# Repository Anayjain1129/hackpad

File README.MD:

# Hack

### Why did I make it?
As I use hyprland user, I really needed a quick way to switch between windows without having using the keyboard shortcuts So ,I designed the Hackpad(hack)

### What was the hardest part about this ?
I had tons of issues with making the Firmware, as I'm on arch linux too I got too many errors. but at the last I figured out everything.

### Bill of Materials
 - 1x Seeed XIAO RP2040
 - 2x LED_SK6812MINI_PLCC4_3.5x3.5mm_P1.75mm
 - 6x SW_Cherry_MX_1.00u_PCB
 - 6x Blank DSA keycaps (Either White or Red)
 - Case (all black or a mix of Black and White)

### Schematic

---

### PCB 

---

### Case
- Bottom

- Top

-Built project

# Youtube Link
https://youtube.com/shorts/4EpmZ8gcD6c?si=dydtyU4dkYbHrrX3

# Reboot changes 
https://drive.google.com/file/d/1OqpE0TkTVKWNDCLAZDDclW11vvze6mBZ/view?usp=sharing

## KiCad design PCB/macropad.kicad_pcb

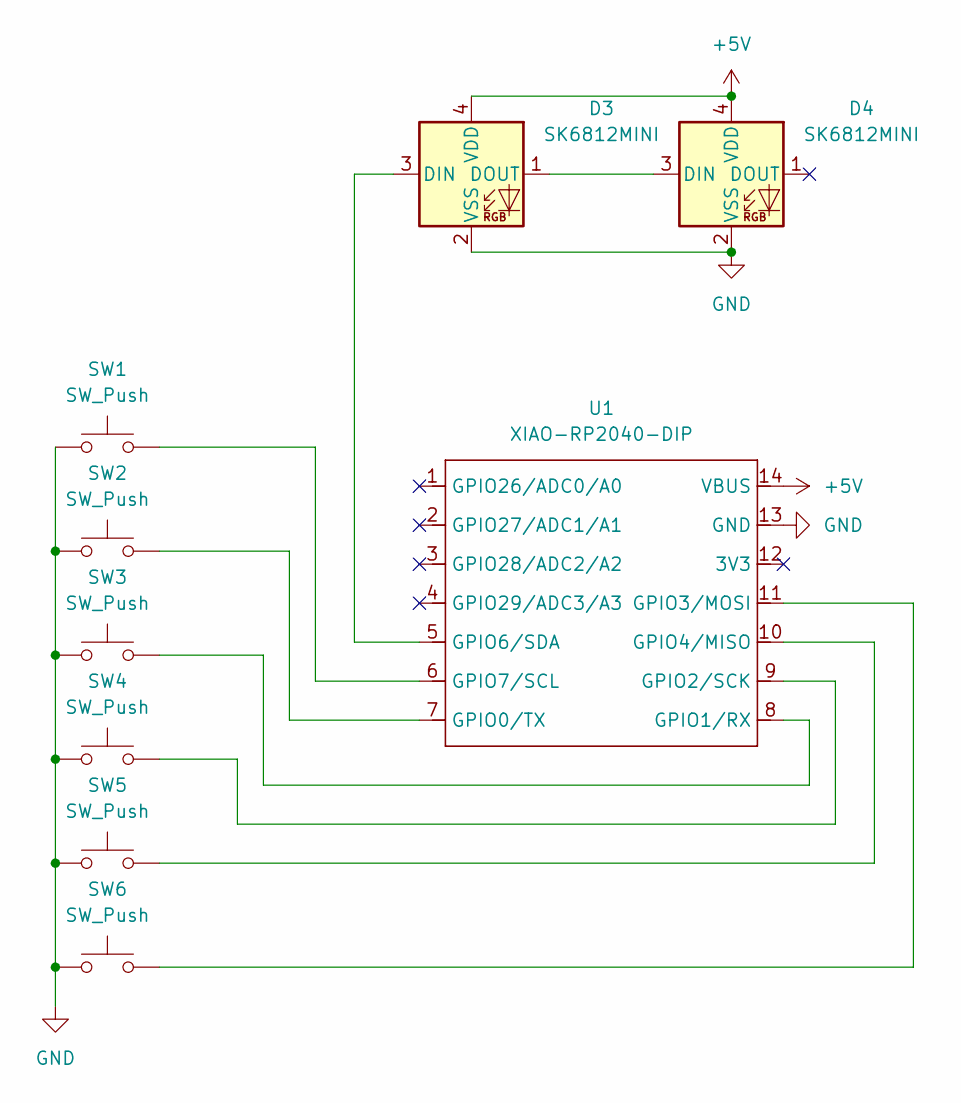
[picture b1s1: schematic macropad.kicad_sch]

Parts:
D3, D4: SK6812MINI; LED_SK6812MINI_PLCC4_3.5x3.5mm_P1.75mm
SW1, SW2, SW3, SW4, SW5, SW6: SW_Push; SW_Cherry_MX_1.00u_PCB
U1: XIAO-RP2040-DIP

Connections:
+5V: D3.4 (VDD), D4.4 (VDD), U1.14 (VBUS)
GND: D3.2 (VSS), D4.2 (VSS), SW1.1, SW2.1, SW3.1, SW4.1, SW5.1, SW6.1, U1.13 (GND)
unnamed: D3.3 (DIN), U1.5 (GPIO6/SDA)
unnamed: D3.1 (DOUT), D4.3 (DIN)
unnamed: SW2.2, U1.7 (GPIO0/TX)
unnamed: SW3.2, U1.8 (GPIO1/RX)
unnamed: SW4.2, U1.9 (GPIO2/SCK)
unnamed: SW6.2, U1.11 (GPIO3/MOSI)
unnamed: SW5.2, U1.10 (GPIO4/MISO)
unnamed: SW1.2, U1.6 (GPIO7/SCL)

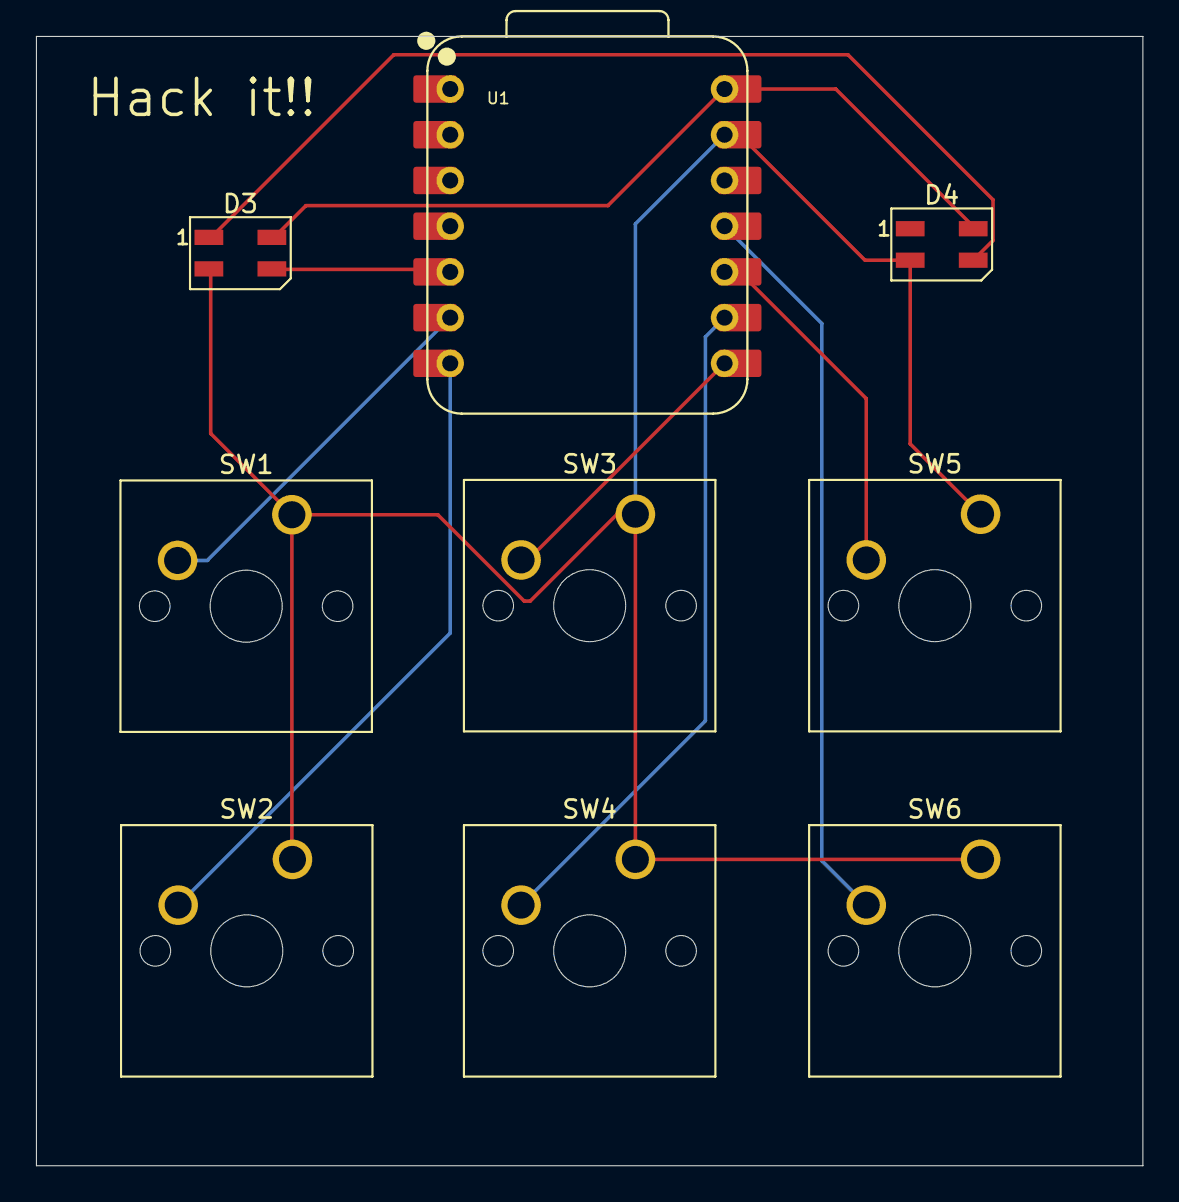
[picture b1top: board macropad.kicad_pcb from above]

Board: 2 copper layers, 61.5 x 62.7 mm, 9 parts (0 on the bottom side), 10 nets.
